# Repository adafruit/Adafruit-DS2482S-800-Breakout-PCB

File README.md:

## Adafruit DS2482S-800 8 Channel I2C to 1-Wire Bus Adapter - STEMMA QT / Qwiic PCB

<a href="http://www.adafruit.com/products/6027"><br/>
Click here to purchase one from the Adafruit shop</a>

PCB files for the Adafruit DS2482S-800 8 Channel I2C to 1-Wire Bus Adapter - STEMMA QT / Qwiic. 

Format is EagleCAD schematic and board layout
* https://www.adafruit.com/product/6027

### Description

This is a DS2482S-800 Stemma QT board that uses a I2C-to-1W controller chip, with 8 selectable channels, built-in parasitic-power-pullups, adjustable I2C address and a wide operating voltage range! You can easily connect it to an existing I2C bus and then use the breakout pads to attach multiple DS18B20's, or pair it with our 1-Wire chaining breakouts for fancier experimentation.

You're probably familiar with the 'top three' electronics protocols: I2C, SPI and UART. Perhaps you're aware of a fourth one, called "1-Wire" which was invented by Dallas Semiconductor (which became Maxim, which became Analog Devices). As you may expect, this protocol uses a single data wire plus a ground wire (and an optional power wire) to connect to any number of sensors or memory chips that all share the same bus.

In theory, there's a lot of different 1-Wire devices out there, but in reality almost everyone uses 1-Wire for DS18B20 temperature sensors. the long wire lengths and ease of 'chaining' by sharing a single bus wire makes it perfectly fine for this purpose. You can bit-bang 1-Wire on most microcontrollers, and some SBCs like Raspberry Pi have kernel module support. But are lots of chips or firmware stacks without 1-Wire capability, or maybe you want to use 1-Wire devices on your desktop computer or other SBC with I2C.

You might be wondering: if you can connect multiple 1-Wire devices on a single wire, then why have 8 channels on this breakout? Reason is: if you have 8 temperature sensors, there's no easy way to know which one is which other than connecting them one at a time and reading the unique ROM identifier. With this breakout you can select the channel so you know for sure which location is being measured, even if the sensor is swapped out later.

To get you going fast, we spun up a custom-made PCB in the STEMMA QT form factor, making it easy to interface. The STEMMA QT connectors on either side are compatible with the SparkFun Qwiic I2C connectors. This allows you to make solderless connections between your development board and the DS2482S-800 or to chain it with a wide range of other sensors and accessories using a compatible cable. You can power the board directly from the STEMMA QT cable, whether 3V or 5V, that voltage will also be the power output for the 1-Wire peripherals.

### License

Adafruit invests time and resources providing this open source design, please support Adafruit and open-source hardware by purchasing products from [Adafruit](https://www.adafruit.com)!

Designed by Limor Fried/Ladyada for Adafruit Industries.

Creative Commons Attribution/Share-Alike, all text above must be included in any redistribution. 
See license.txt for additional details.

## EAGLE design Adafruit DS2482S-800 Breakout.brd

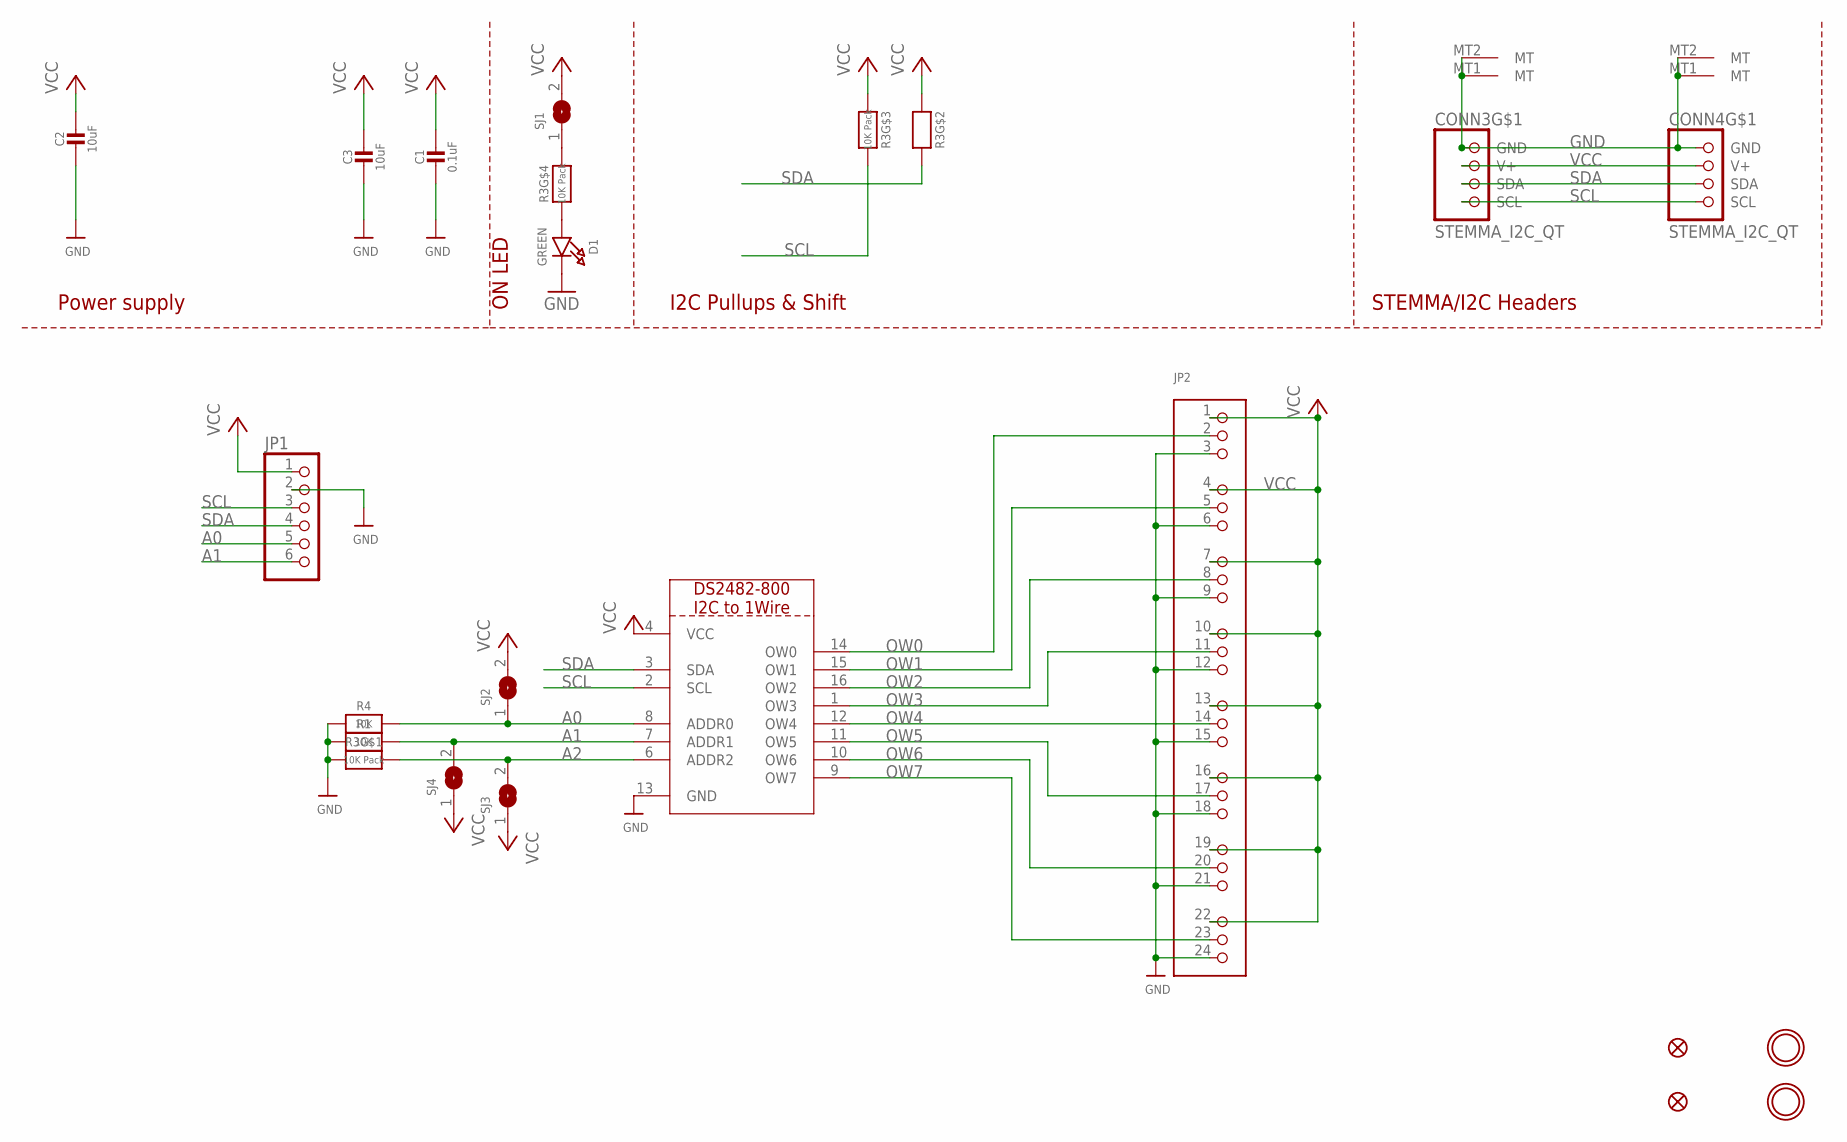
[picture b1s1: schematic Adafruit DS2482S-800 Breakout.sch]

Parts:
C1: 0.1uF; 0603-NO
C2, C3: 10uF; 0805-NO
CONN3, CONN4: STEMMA_I2C_QT; JST_SH4
D1: GREEN; CHIPLED_0603_NOOUTLINE
FID3, FID4: FIDUCIAL_1MM
JP1: HEADER-1X670MIL; 1X06_ROUND_70
JP2: HEADER-3X08; 3X08
R1, R4: 10K; 0603-NO
R3: 10K Pack; RESPACK_4X0603
SJ1: SOLDERJUMPERCLOSED; SOLDERJUMPER_CLOSEDWIRE
SJ2, SJ3, SJ4: SOLDERJUMPER; SOLDERJUMPER_ARROW_NOPASTE
U$19, U$21: MOUNTINGHOLE2.5; MOUNTINGHOLE_2.5_PLATED
X1: DS2482-800; SO16

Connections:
A0: JP1.5, R4.2, SJ2.1, X1.8 (ADDR0)
A1: JP1.6, R1.2, SJ4.2, X1.7 (ADDR1)
A2: R3.8 (2), SJ3.2, X1.6 (ADDR2)
GND: C1.2, C2.2, C3.2, CONN3.1 (GND), CONN3.MT1 (MT), CONN3.MT2 (MT), CONN4.1 (GND), CONN4.MT1 (MT), CONN4.MT2 (MT), D1.C, JP1.2, JP2.3, JP2.6, JP2.9, JP2.12, JP2.15, JP2.18, JP2.21, JP2.24, R1.1, R3.1, R4.1, X1.13 (GND)
unnamed: D1.A, R3.4 (1)
unnamed: R3.5 (2), SJ1.1
OW0: JP2.2, X1.14 (OW0)
OW1: JP2.5, X1.15 (OW1)
OW2: JP2.8, X1.16 (OW2)
OW3: JP2.11, X1.1 (OW3)
OW4: JP2.14, X1.12 (OW4)
OW5: JP2.17, X1.11 (OW5)
OW6: JP2.20, X1.10 (OW6)
OW7: JP2.23, X1.9 (OW7)
SCL: CONN3.4 (SCL), CONN4.4 (SCL), JP1.3, R3.6 (2), X1.2 (SCL)
SDA: CONN3.3 (SDA), CONN4.3 (SDA), JP1.4, R3.7 (2), X1.3 (SDA)
VCC: C1.1, C2.1, C3.1, CONN3.2 (V+), CONN4.2 (V+), JP1.1, JP2.1, JP2.4, JP2.7, JP2.10, JP2.13, JP2.16, JP2.19, JP2.22, R3.2 (1), R3.3 (1), SJ1.2, SJ2.2, SJ3.1, SJ4.1, X1.4 (VCC)

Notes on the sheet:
I2C Pullups & Shift
STEMMA/I2C Headers
ON LED
Power supply

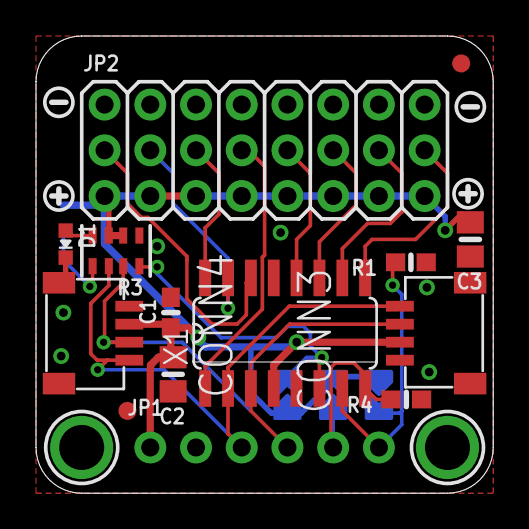
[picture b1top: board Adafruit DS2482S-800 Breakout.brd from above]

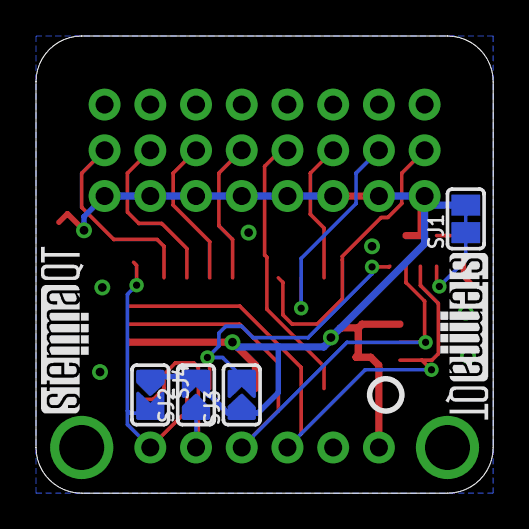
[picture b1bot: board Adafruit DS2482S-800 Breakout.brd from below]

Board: 2 copper layers, 25.4 x 25.4 mm, 51 parts (13 on the bottom side), 17 nets.

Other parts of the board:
PLABEL0: PLABEL0
PLABEL1: PLABEL1
PLABEL2: PLABEL2
PLABEL3: PLABEL3
PLABEL4: PLABEL4
PLABEL5: PLABEL5
PLABEL6: PLABEL6
PLABEL7: PLABEL7
PLABEL8: PLABEL8
PLABEL9: PLABEL9
PLABEL10: PLABEL10
PLABEL11: PLABEL11
PLABEL12: PLABEL12
PLABEL13: PLABEL13
PLABEL14: PLABEL14
PLABEL15: PLABEL15
PLABEL16: PLABEL16
PLABEL17: PLABEL17
PLABEL18: PLABEL18
PLABEL19: PLABEL19
PLABEL20: PLABEL20
PLABEL21: PLABEL21
PLABEL22: PLABEL22
PLABEL23: PLABEL23
U$4, U$7: SYMBOL_MINUS
U$8, U$9: SYMBOL_PLUS
U$25: PCBFEAT-REV-040
U$30, U$31: STEMMAQT

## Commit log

2024-09-17 cookiecutter

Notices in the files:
parts and their libraries:
microbuilder: This work is placed in the public domain, and may be freely used for commercial and non-commercial work with the following conditions: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
